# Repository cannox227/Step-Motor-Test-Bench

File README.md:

# Step-motor-test-bench

Step Motor Testbench is a tool made in collaboration with [ProM Facility](https://promfacility.eu/#/) which can be used to measure the __maximum power__ and the __maximum torque__ of a step motor. <br>
Notice that this is a prototype made up to validate the innovative company idea. 

## Functionalities
1. Driving the stepper motor
2. Driving the magnetic brake
3. Measuring the involved physical quantities such as: torque, voltage and current of the motor
4. Set the motor driver parameters and show the plots related to the obtained motor curves using a GUI (Graphical User Interface)

## Main components
- Step motor (device under test)
- Torque sensor
- Magnetic brake
- Master unit made of
    - Nucleo STM32 F7 Board
    - Custom PCB to handle different voltages and conditionate the signals
- Slave unit made of
    - Nucleo STM32 F4 Board
    - STM X-NUCLEO-IHM03A1 stepper driver extension board

## System block diagram

## Thesis abstract
This thesis reports the work done during my internship period at ProM Facility, the company - based in Rovereto (TN) - is focused on mechanics, electronics and informatics prototyping. This work principally covers the high level software development and at the same time the baremetal firmware development to support the innovative company project. In particular, ProM Facility had the necessity to prototype a __stepper motor test bench__ for an internal usage. This measurement tool is able to determine the __maximum power__ and __maximum torque__ provided by the under test motor.

At my arrival in the company the test bench mechanical structure was already built, ensuring the connection between a magnetic brake, a torque sensor and a stepper motor. To make the prototype actually working it has been necessary to integrate the hardware development with the software one. Obtaining the characteristic curves that describes the performance of the motor has been one of the main objectives of my work, in order to get this results sensors of voltage, current and torque have been used. Moreover, a wide variety of motor driver parameters selection has been implemented, in such a way to build a custom configuration with the purpose of optimize the produced curves by operating on the single parameters. However, this curve optimization task will be studied by the future company interns.

It has also been developed a dedicated graphical user interface to let the end user interacting with the test bench, with this software it is possible to change the motor driver parameters and test it under load; on the other hand, to read the sensors values and drive the motor, two units have been projected: _master_ and _slave_. The first one is made up of a _STM Nucleo F7_ board with a custom developed _shield_, where sensors and signal conditioning circuits have been soldered. The second one, instead, is composed of a _STM Nucleo F4_ board and an expansion driver board - the _STM X-NUCLEO-IHM03A1_ - necessary to control the motor under the F4 _microcontroller_ rules.

The thesis especially describes the development process to create the graphical interface using the Python programming language and to write the firmware of the master unit. For the last one a duo formed by the STM Cube MX software and the C language has been selected. Eventually, the remaining work, consisting of the slave firmware development and the prototyping of the expansion board for the master unit, has been up to the colleague with whom I have shared the internship experience, _Lisa Santarossa_.

As planned, the project has been concluded successfully, gathering the curves of __torque-power__ based on the custom configuration chosen by the end user.

__You can find the theseis [here](/Documentation/Tommaso_Canova_STB_thesis.pdf)__

## Repo structure
    ├── 📁 Documentation    -> media and thesis
    ├── 📁 Firmware         -> slave and master units firmware
    ├── 📁 GUI              -> graphical user iterface and plot scripts
    └── 📁 Hardware         -> custom master unit expansion board kicad project

## GUI screenshots
The GUI is made up of two main windows: the first one is used to control the motor driver parameters, to test the motor under load, to communicate with both units using serial communication and to save the acquired data into a csv file. The second one is used to plot the acquired data into some.

The second one is used to read the sensors values and to plot the acquired data in a dynamic way.

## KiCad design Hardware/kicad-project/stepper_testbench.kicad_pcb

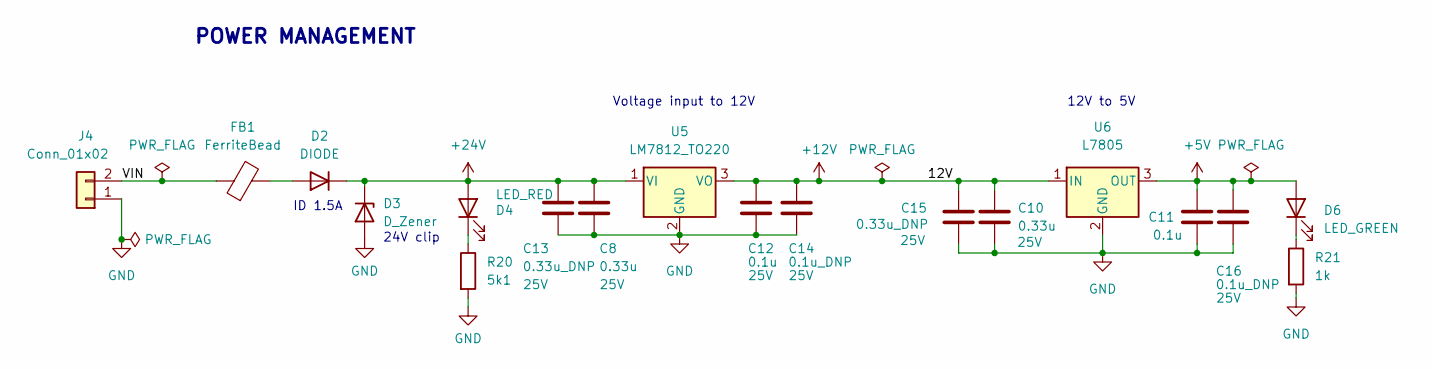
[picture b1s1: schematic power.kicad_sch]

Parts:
C8, C10: 0.33u; C_0603_1608Metric
C11, C12: 0.1u; C_0603_1608Metric
C13, C15: 0.33u_DNP; CP_Radial_D5.0mm_P2.50mm
C14, C16: 0.1u_DNP; CP_Radial_D5.0mm_P2.50mm
D2: DIODE; D_SOD-323
D3: D_Zener; D_SMA
D4: LED_RED; LED_0603_1608Metric
D6: LED_GREEN; LED_0603_1608Metric
FB1: FerriteBead; R_0805_2012Metric
J4: Conn_01x02; PinHeader_1x02_P2.54mm_Vertical
R20: 5k1; R_0603_1608Metric
R21: 1k; R_0603_1608Metric
U5: LM7812_TO220; TO-220-3_Vertical
U6: L7805; TO-220-3_Vertical

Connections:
+5V: C11.1, C16.1, D6.2 (A), U6.3 (OUT); also elsewhere on the board
+12V: C10.1, C12.1, C14.1, C15.1, U5.3 (VO), U6.1 (IN); also elsewhere on the board
+24V: C8.1, C13.1, D2.2 (K), D3.1 (K), D4.2 (A), U5.1 (VI); also elsewhere on the board
/Power/VIN: FB1.1, J4.2
GND: C8.2, C10.2, C11.2, C12.2, C13.2, C14.2, C15.2, C16.2, D3.2 (A), J4.1, R20.2, R21.2, U5.2 (GND), U6.2 (GND); also elsewhere on the board
unnamed: D2.1 (A), FB1.2
unnamed: D4.1 (K), R20.1
unnamed: D6.1 (K), R21.1

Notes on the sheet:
Voltage input to 12V
POWER MANAGEMENT
24V clip
12V to 5V
ID 1.5A

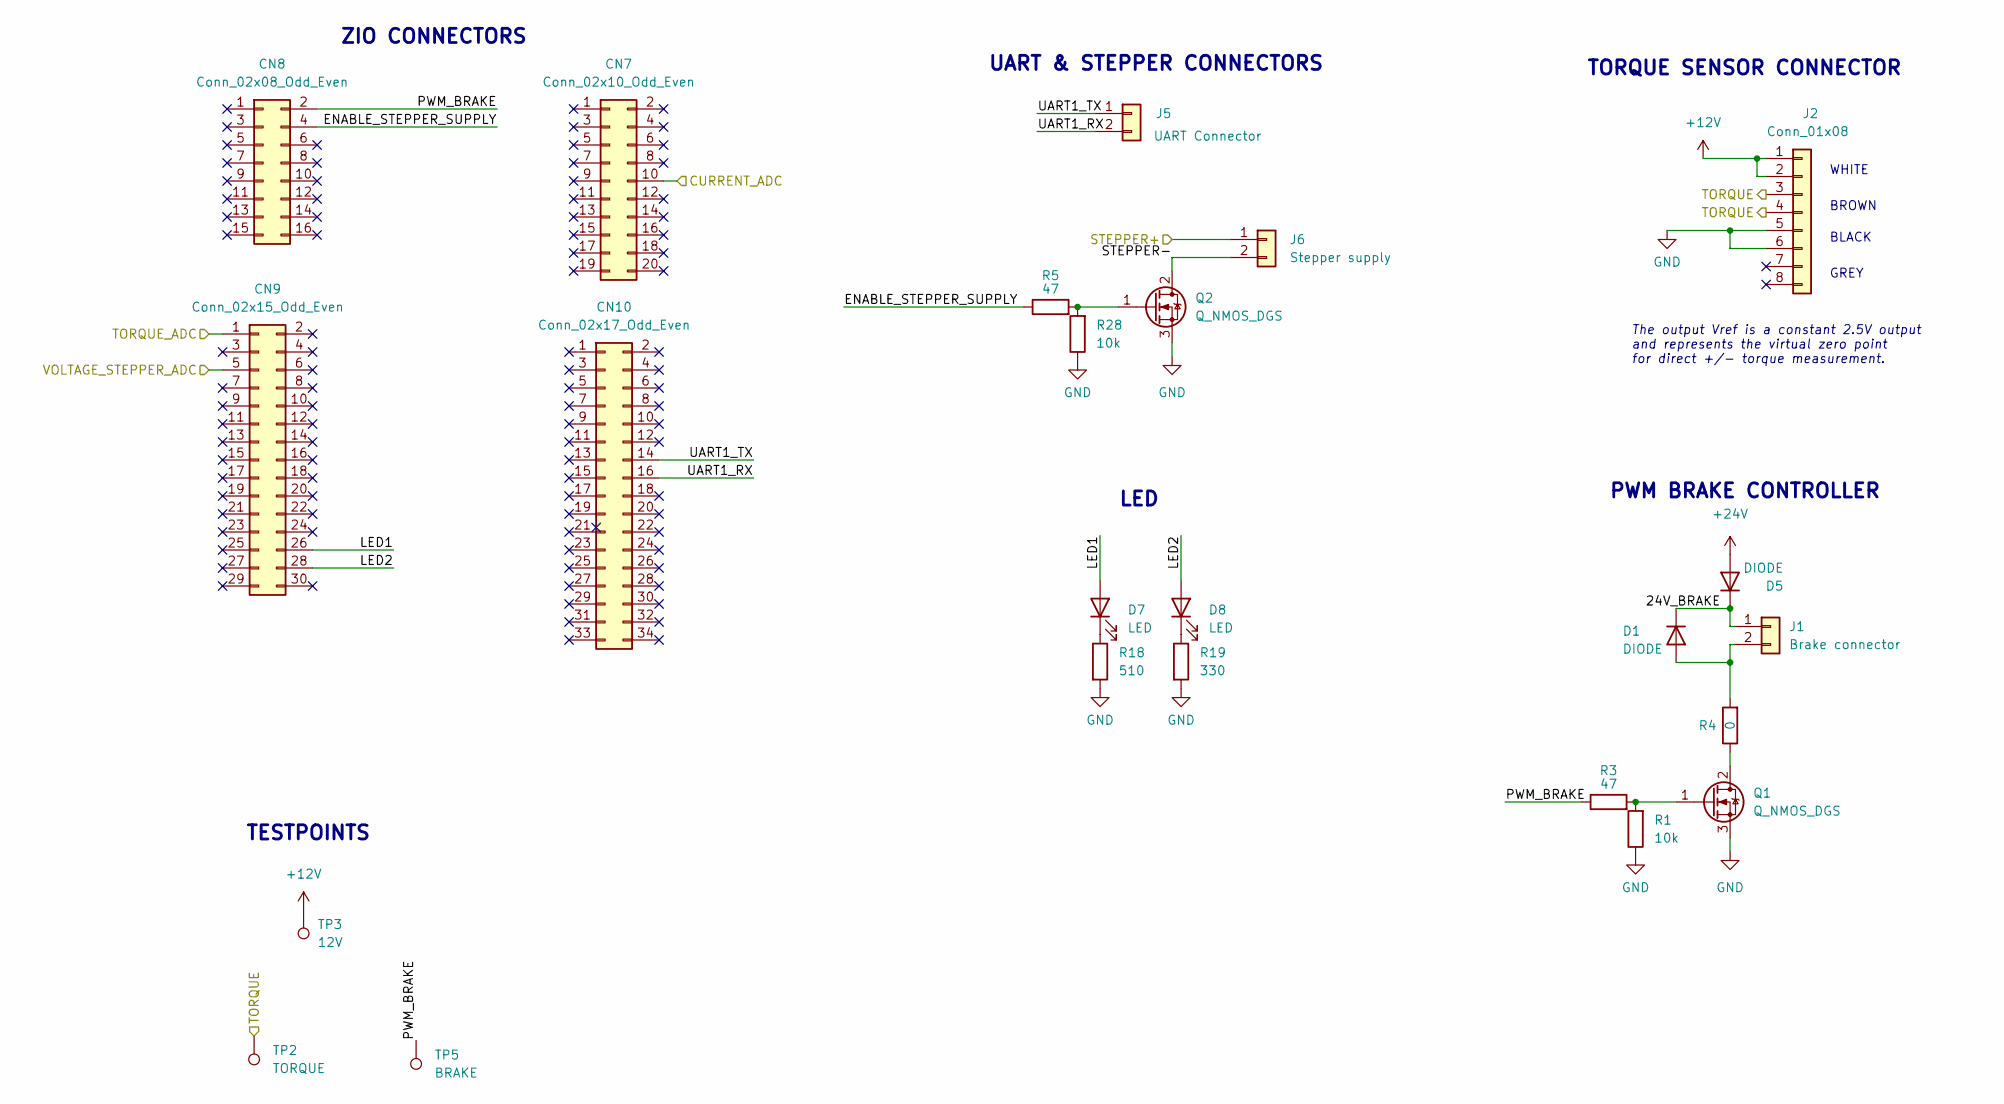
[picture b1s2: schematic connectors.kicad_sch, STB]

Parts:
CN7: Conn_02x10_Odd_Even; PinHeader_2x10_P2.54mm_Vertical
CN8: Conn_02x08_Odd_Even; PinHeader_2x08_P2.54mm_Vertical
CN9: Conn_02x15_Odd_Even; PinHeader_2x15_P2.54mm_Vertical
CN10: Conn_02x17_Odd_Even; PinHeader_2x17_P2.54mm_Vertical
D1, D5: DIODE; D_SOD-323
D7, D8: LED; LED_0603_1608Metric
J1: Brake connector; PinHeader_1x02_P2.54mm_Vertical
J2: Conn_01x08; PinHeader_1x08_P2.54mm_Vertical
J5: UART Connector; PinHeader_1x02_P2.54mm_Vertical
J6: Stepper supply; PinHeader_1x02_P2.54mm_Vertical
Q1, Q2: Q_NMOS_DGS; TO-252-2
R1, R28: 10k; R_0603_1608Metric
R3, R5: 47; R_0603_1608Metric
R4: 0; R_0603_1608Metric
R18: 510; R_0603_1608Metric
R19: 330; R_0603_1608Metric
TP2: TORQUE; TestPoint_Pad_D2.0mm
TP3: 12V; TestPoint_Pad_D2.0mm
TP5: BRAKE; TestPoint_Pad_D2.0mm

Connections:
+12V: J2.1, J2.2, TP3.1; also elsewhere on the board
+24V: D5.1 (A); also elsewhere on the board
/Connectors/24V_BRAKE: D1.2 (K), D5.2 (K), J1.1
/Connectors/ENABLE_STEPPER_SUPPLY: CN8.4, R5.1
/Connectors/LED1: CN9.26, D7.2 (A)
/Connectors/LED2: CN9.28, D8.2 (A)
/Connectors/PWM_BRAKE: CN8.2, R3.1, TP5.1
/Connectors/STEPPER+: J6.1; also elsewhere on the board
/Connectors/TORQUE: J2.3, J2.4, TP2.1; also elsewhere on the board
/Connectors/UART1_RX: CN10.16, J5.2
/Connectors/UART1_TX: CN10.14, J5.1
/Sensing/CURRENT_BUFF_ADC: CN7.10; also elsewhere on the board
/Sensing/TORQUE_BUFF_ADC: CN9.1; also elsewhere on the board
/Sensing/VOLTAGE_STEPPER_BUFF_ADC: CN9.5; also elsewhere on the board
GND: J2.5, J2.6, Q1.3 (S), Q2.3 (S), R1.1, R18.2, R19.2, R28.1; also elsewhere on the board
unnamed: D1.1 (A), J1.2, R4.2
unnamed: D7.1 (K), R18.1
unnamed: D8.1 (K), R19.1
unnamed: Q1.1 (G), R1.2, R3.2
unnamed: Q1.2 (D), R4.1
unnamed: Q2.1 (G), R5.2, R28.2
unnamed: J6.2, Q2.2 (D)

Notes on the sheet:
LED
TORQUE SENSOR CONNECTOR
BROWN
BLACK
WHITE
GREY
The output Vref is a constant 2.5V output and represents the virtual zero point for direct +/- torque measurement.
UART & STEPPER CONNECTORS
TESTPOINTS
ZIO CONNECTORS
PWM BRAKE CONTROLLER

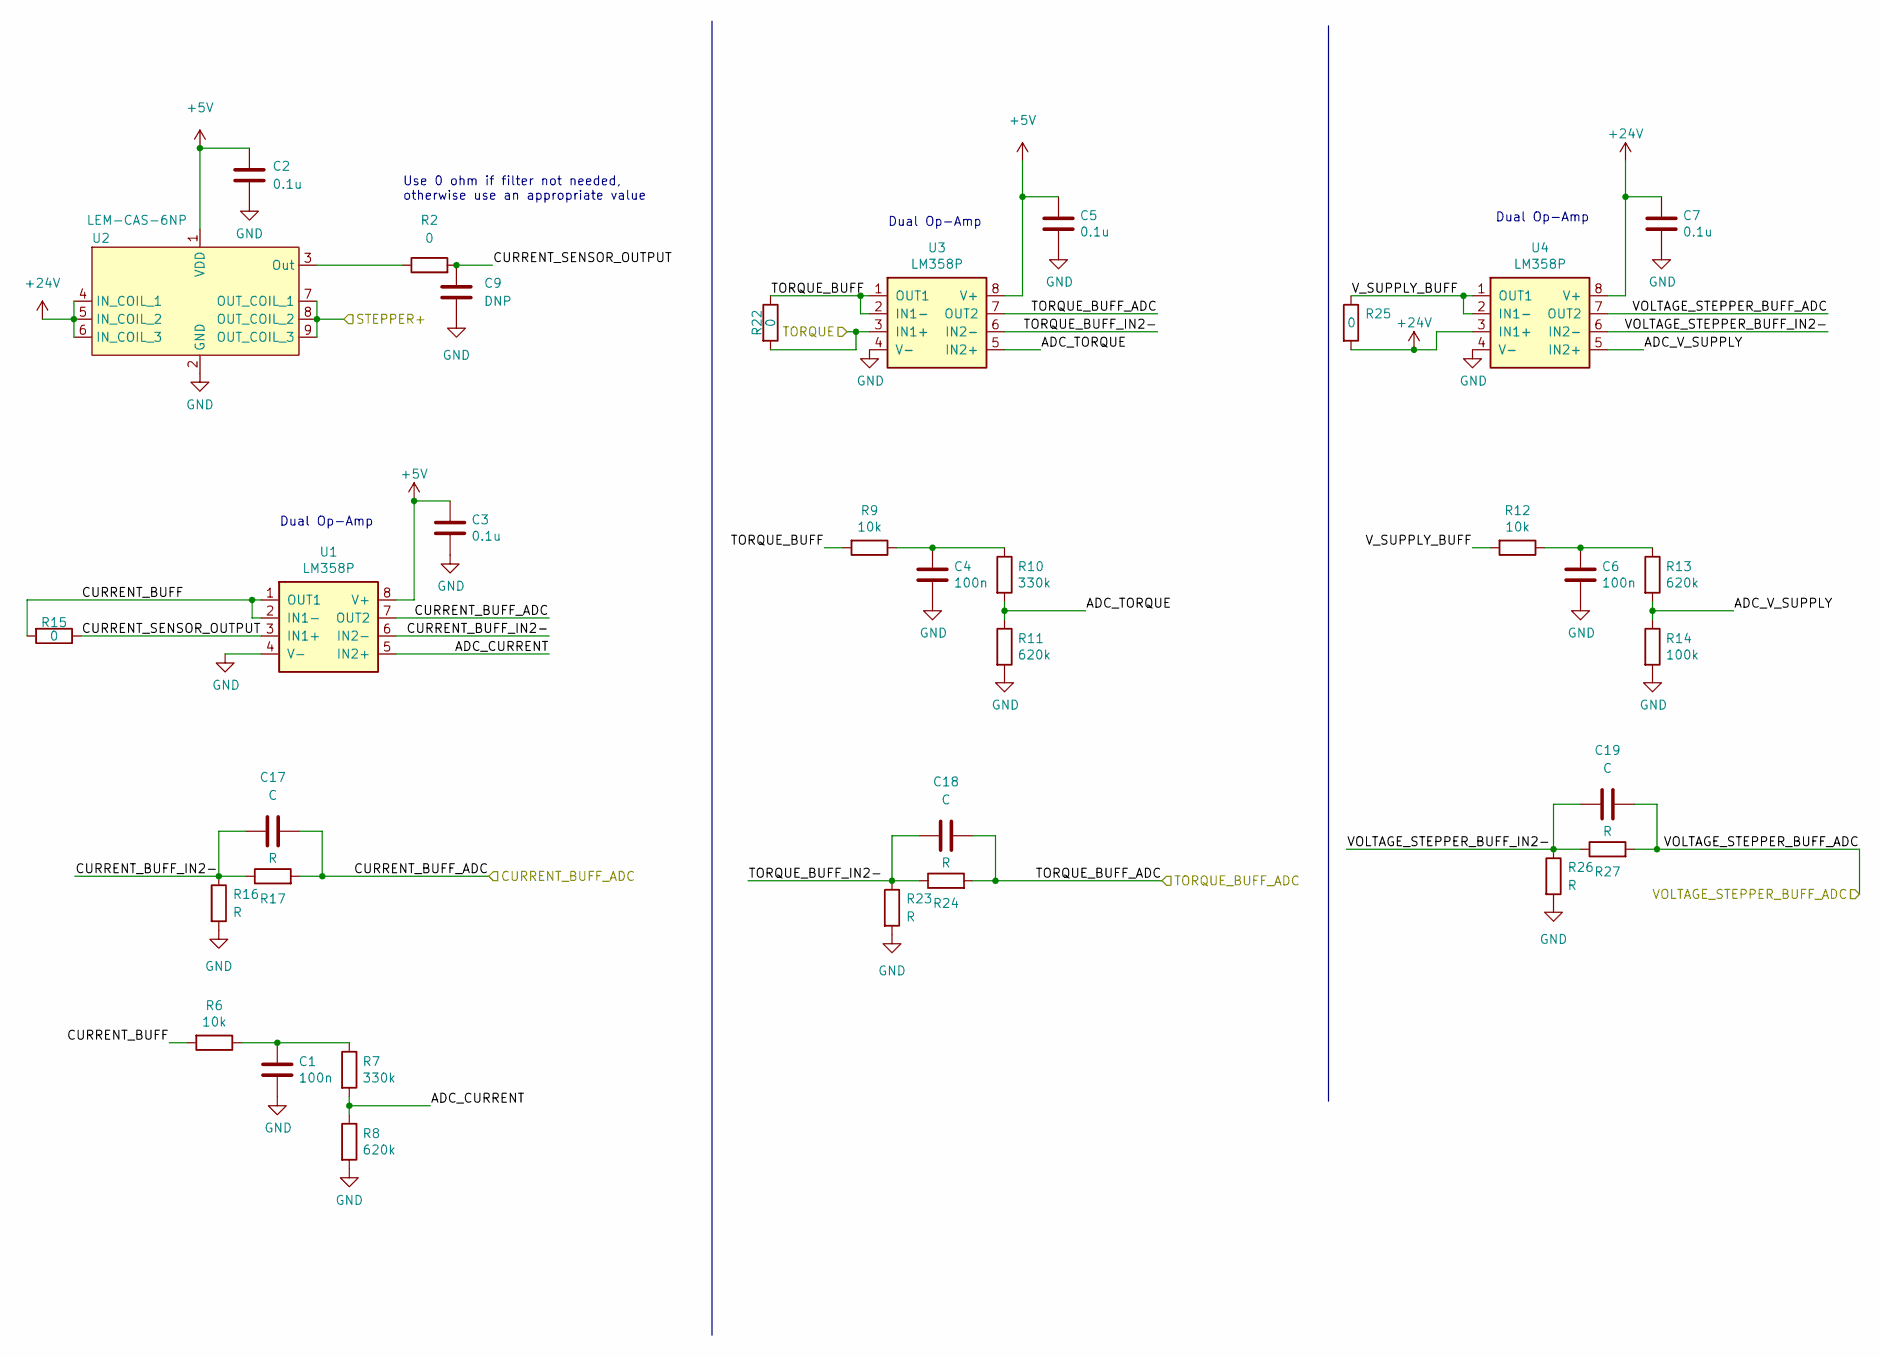
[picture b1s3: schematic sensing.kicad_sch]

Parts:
C1, C4, C6: 100n; C_0603_1608Metric
C2, C3, C5, C7: 0.1u; C_0603_1608Metric
C9: DNP; C_0805_2012Metric
C17, C18, C19: C; C_0805_2012Metric
R2, R15, R22, R25: 0; R_0603_1608Metric
R6, R9, R12: 10k; R_0603_1608Metric
R7, R10: 330k; R_0603_1608Metric
R8, R11, R13: 620k; R_0603_1608Metric
R14: 100k; R_0603_1608Metric
R16, R17, R23, R24, R26, R27: R; R_0603_1608Metric
U1, U3, U4: LM358P; DIP-8_W7.62mm
U2: LEM-CAS-6NP; LEM-CAS-6-NP

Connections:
+5V: C2.1, C3.1, C5.1, U1.8 (V+), U2.1 (VDD), U3.8 (V+); also elsewhere on the board
+24V: C7.1, R25.2, U2.4 (IN_COIL_1), U2.5 (IN_COIL_2), U2.6 (IN_COIL_3), U4.3 (IN1+), U4.8 (V+); also elsewhere on the board
/Connectors/STEPPER+: U2.7 (OUT_COIL_1), U2.8 (OUT_COIL_2), U2.9 (OUT_COIL_3); also elsewhere on the board
/Connectors/TORQUE: R22.2, U3.3 (IN1+); also elsewhere on the board
/Sensing/ADC_CURRENT: R7.2, R8.1, U1.5 (IN2+)
/Sensing/ADC_TORQUE: R10.2, R11.1, U3.5 (IN2+)
/Sensing/ADC_V_SUPPLY: R13.2, R14.1, U4.5 (IN2+)
/Sensing/CURRENT_BUFF: R6.2, R15.2, U1.1 (OUT1), U1.2 (IN1-)
/Sensing/CURRENT_BUFF_ADC: C17.1, R17.2, U1.7 (OUT2); also elsewhere on the board
/Sensing/CURRENT_BUFF_IN2-: C17.2, R16.1, R17.1, U1.6 (IN2-)
/Sensing/CURRENT_SENSOR_OUTPUT: C9.1, R2.2, R15.1, U1.3 (IN1+)
/Sensing/TORQUE_BUFF: R9.2, R22.1, U3.1 (OUT1), U3.2 (IN1-)
/Sensing/TORQUE_BUFF_ADC: C18.1, R24.2, U3.7 (OUT2); also elsewhere on the board
/Sensing/TORQUE_BUFF_IN2-: C18.2, R23.1, R24.1, U3.6 (IN2-)
/Sensing/VOLTAGE_STEPPER_BUFF_ADC: C19.1, R27.2, U4.7 (OUT2); also elsewhere on the board
/Sensing/VOLTAGE_STEPPER_BUFF_IN2-: C19.2, R26.1, R27.1, U4.6 (IN2-)
/Sensing/V_SUPPLY_BUFF: R12.2, R25.1, U4.1 (OUT1), U4.2 (IN1-)
GND: C1.2, C2.2, C3.2, C4.2, C5.2, C6.2, C7.2, C9.2, R8.2, R11.2, R14.2, R16.2, R23.2, R26.2, U1.4 (V-), U2.2 (GND), U3.4 (V-), U4.4 (V-); also elsewhere on the board
unnamed: C1.1, R6.1, R7.1
unnamed: C4.1, R9.1, R10.1
unnamed: C6.1, R12.1, R13.1
unnamed: R2.1, U2.3 (Out)

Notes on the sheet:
Dual Op-Amp
Use 0 ohm if filter not needed, otherwise use an appropriate value

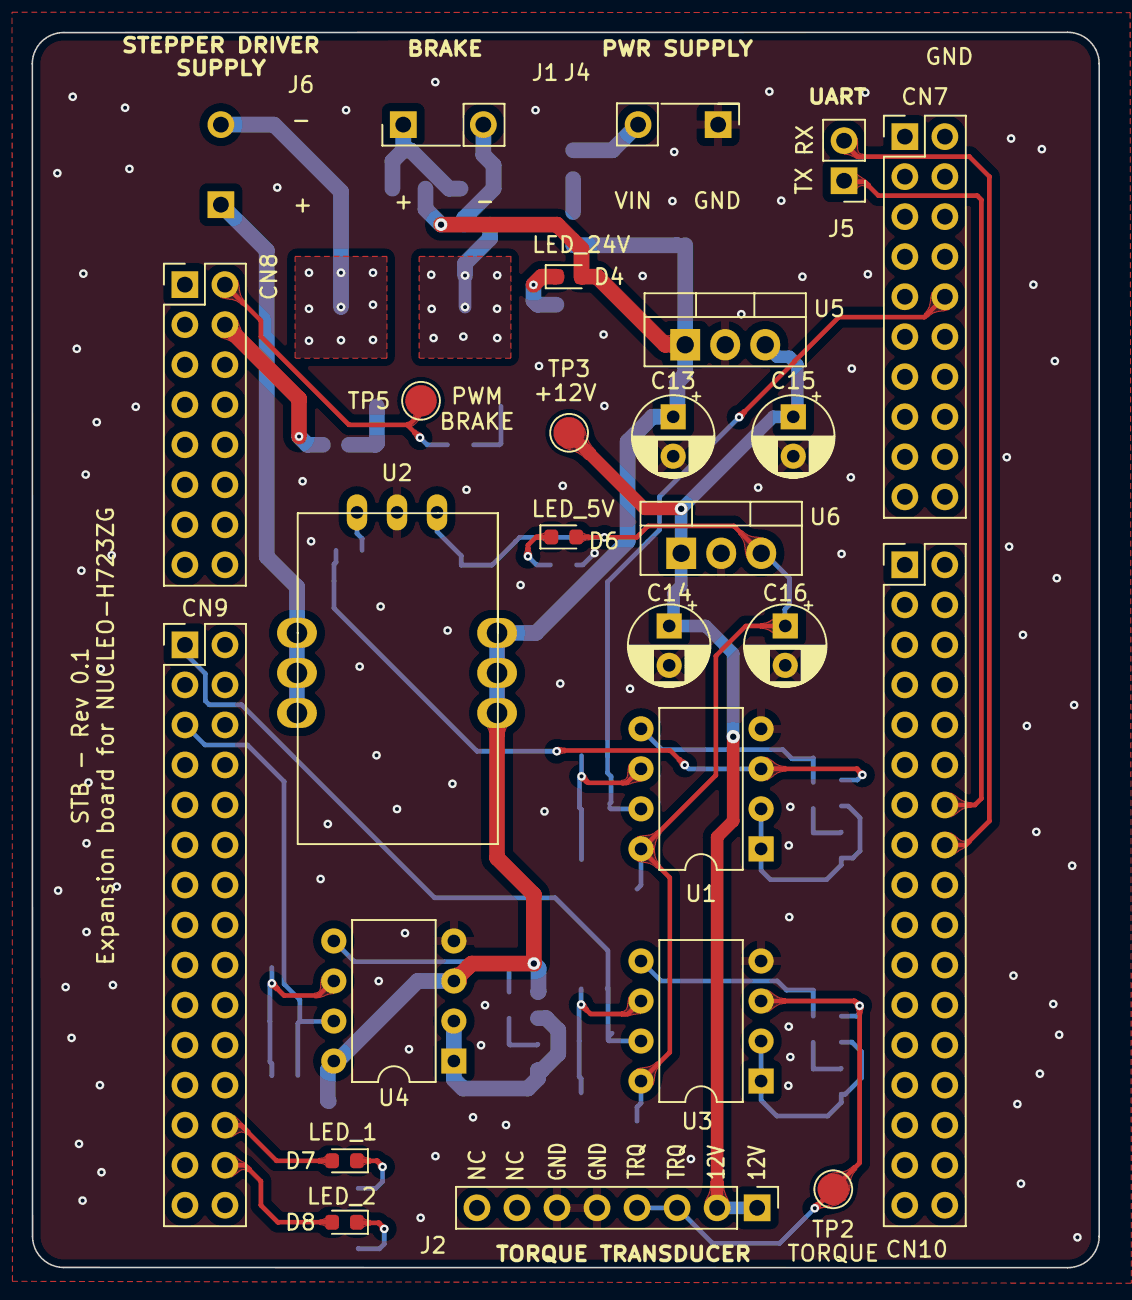
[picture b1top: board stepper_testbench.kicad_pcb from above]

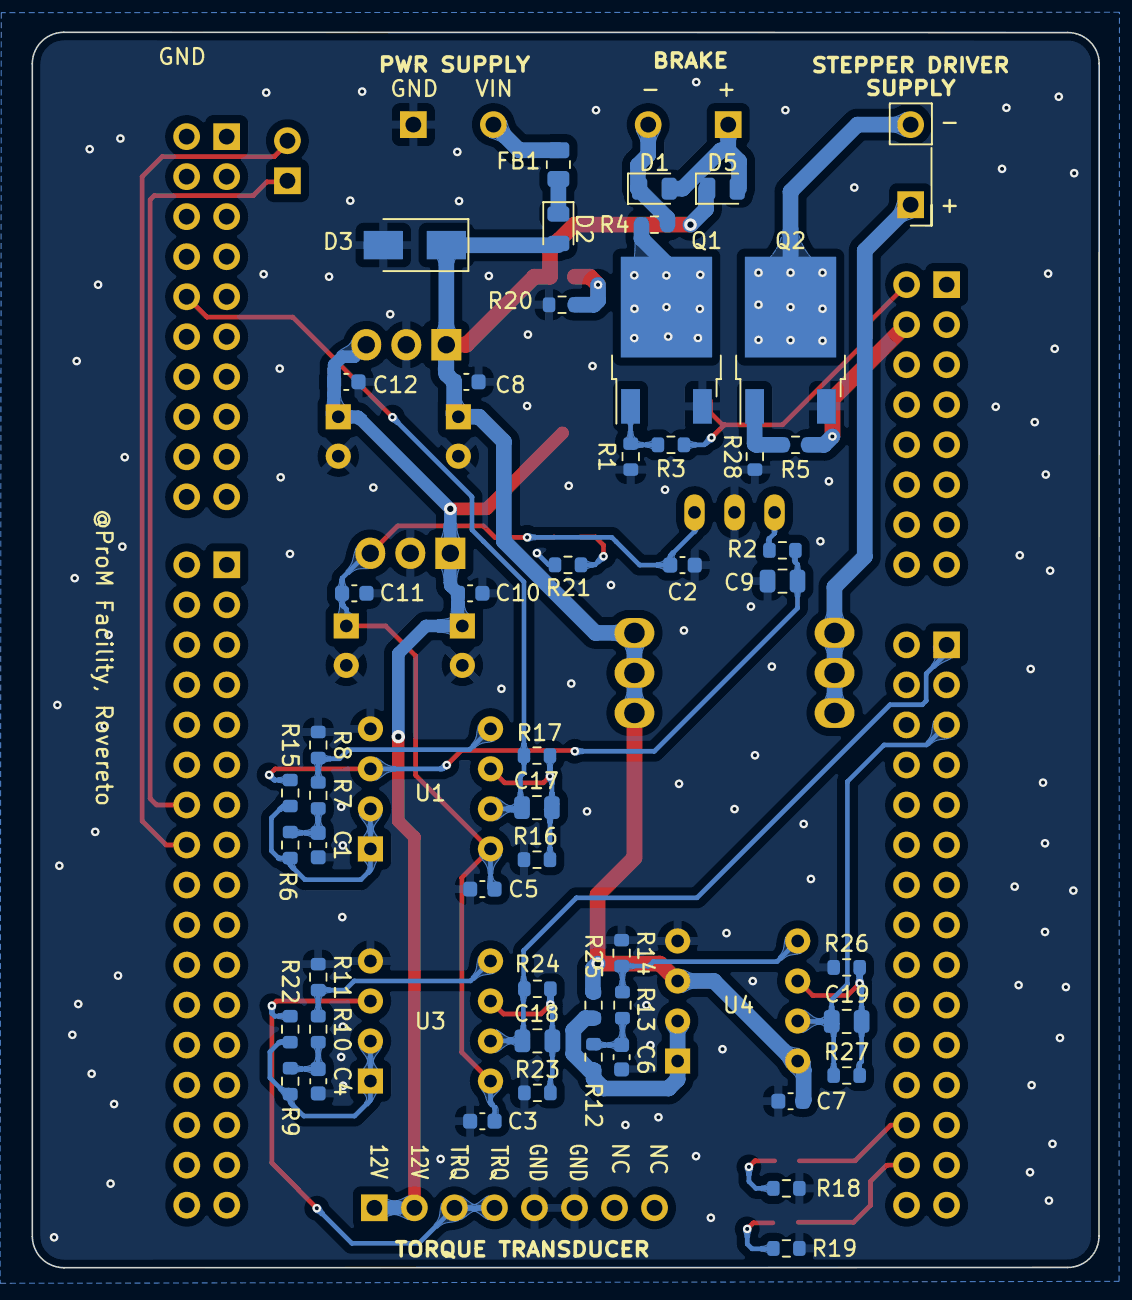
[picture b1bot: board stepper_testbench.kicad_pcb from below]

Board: 2 copper layers, 67.7 x 78.4 mm, 76 parts (55 on the bottom side), 41 nets.

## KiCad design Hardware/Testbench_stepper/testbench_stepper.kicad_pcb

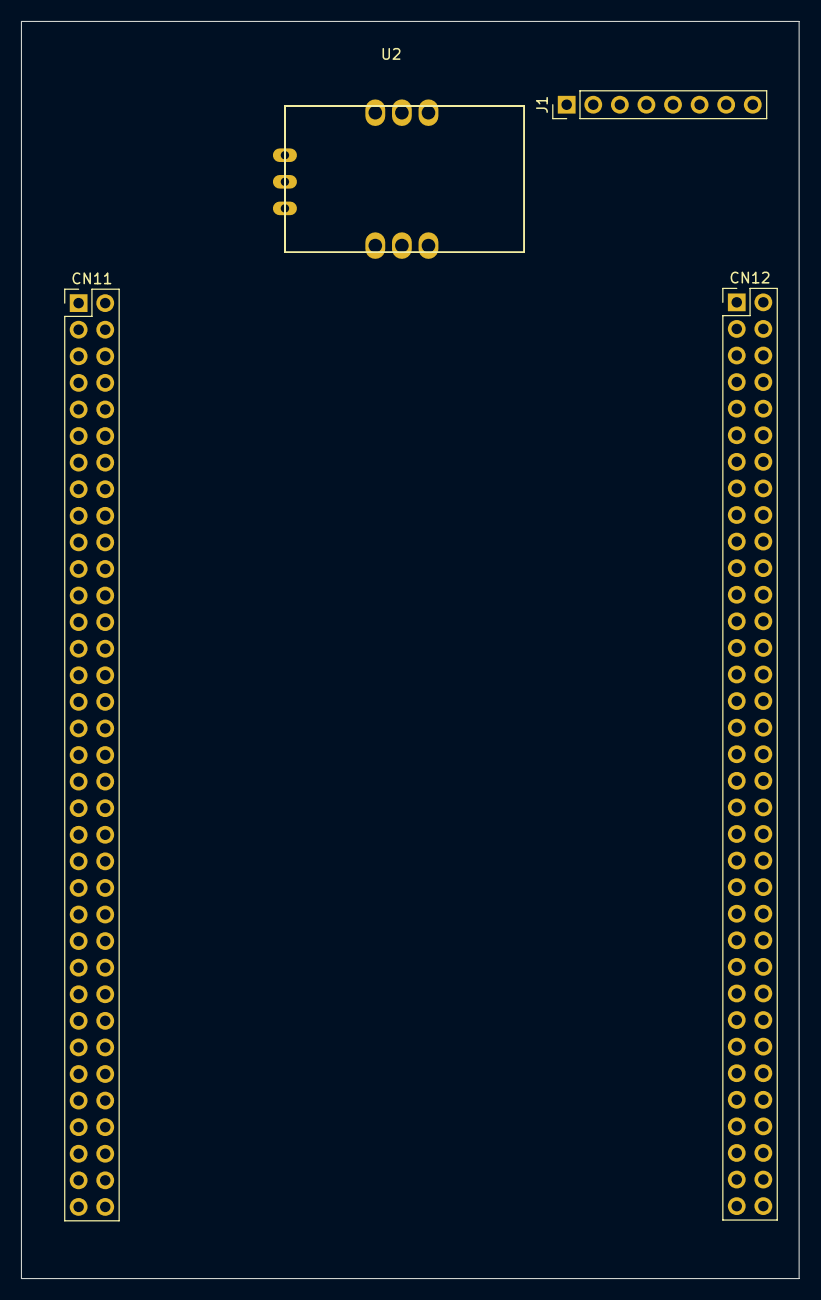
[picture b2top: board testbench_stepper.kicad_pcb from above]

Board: 2 copper layers, 74.3 x 120.1 mm, 4 parts (0 on the bottom side), 4 nets, no tracks yet.

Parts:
CN11, CN12: Conn_02x35_Odd_Even; PinHeader_2x35_P2.54mm_Vertical
J1: Conn_01x08_Male; PinHeader_1x08_P2.54mm_Vertical
U2: LEM-CAS-6-NP

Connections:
/Connectors/GND: J1.5, J1.6
/Connectors/TRQ: J1.3, J1.4
/Connectors/VDD: J1.1, J1.2
/Connectors/VREF: J1.7, J1.8

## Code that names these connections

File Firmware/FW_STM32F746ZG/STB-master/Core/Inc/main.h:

/* USER CODE BEGIN Header */
/**
  ******************************************************************************
  * @file           : main.h
  * @brief          : Header for main.c file.
  *                   This file contains the common defines of the application.
  ******************************************************************************
  * @attention
  *
  * Copyright (c) 2022 STMicroelectronics.
  * All rights reserved.
  *
  * This software is licensed under terms that can be found in the LICENSE file
  * in the root directory of this software component.
  * If no LICENSE file comes with this software, it is provided AS-IS.
  *
  ******************************************************************************
  */
/* USER CODE END Header */

/* Define to prevent recursive inclusion -------------------------------------*/
#ifndef __MAIN_H
#define __MAIN_H

#ifdef __cplusplus
extern "C" {
#endif

/* Includes ------------------------------------------------------------------*/
#include "stm32f7xx_hal.h"

/* Private includes ----------------------------------------------------------*/
/* USER CODE BEGIN Includes */
#include "tim.h"
/* USER CODE END Includes */

/* Exported types ------------------------------------------------------------*/
/* USER CODE BEGIN ET */

/* USER CODE END ET */

/* Exported constants --------------------------------------------------------*/
/* USER CODE BEGIN EC */

/* USER CODE END EC */

/* Exported macro ------------------------------------------------------------*/
/* USER CODE BEGIN EM */

/* USER CODE END EM */

/* Exported functions prototypes ---------------------------------------------*/
void Error_Handler(void);

/* USER CODE BEGIN EFP */
extern float brake_single_step_period;
/* USER CODE END EFP */

/* Private defines -----------------------------------------------------------*/
#define USER_Btn_Pin GPIO_PIN_13
#define USER_Btn_GPIO_Port GPIOC
#define LED1_Pin GPIO_PIN_7
#define LED1_GPIO_Port GPIOF
#define LED2_Pin GPIO_PIN_9
#define LED2_GPIO_Port GPIOF
#define MCO_Pin GPIO_PIN_0
#define MCO_GPIO_Port GPIOH
#define STEPPER_VOLTAGE_ADC_Pin GPIO_PIN_3
#define STEPPER_VOLTAGE_ADC_GPIO_Port GPIOC
#define TORQUE_ADC_Pin GPIO_PIN_3
#define TORQUE_ADC_GPIO_Port GPIOA
#define CURRENT_ADC_Pin GPIO_PIN_5
#define CURRENT_ADC_GPIO_Port GPIOA
#define LD1_Pin GPIO_PIN_0
#define LD1_GPIO_Port GPIOB
#define DEBUG_SIGNAL_2_Pin GPIO_PIN_0
#define DEBUG_SIGNAL_2_GPIO_Port GPIOG
#define LD3_Pin GPIO_PIN_14
#define LD3_GPIO_Port GPIOB
#define STLK_RX_Pin GPIO_PIN_8
#define STLK_RX_GPIO_Port GPIOD
#define STLK_TX_Pin GPIO_PIN_9
#define STLK_TX_GPIO_Port GPIOD
#define USB_PowerSwitchOn_Pin GPIO_PIN_6
#define USB_PowerSwitchOn_GPIO_Port GPIOG
#define USB_OverCurrent_Pin GPIO_PIN_7
#define USB_OverCurrent_GPIO_Port GPIOG
#define PWM_BRAKE_Pin GPIO_PIN_8
#define PWM_BRAKE_GPIO_Port GPIOC
#define ENABLE_STEPPER_SUPPLY_Pin GPIO_PIN_9
#define ENABLE_STEPPER_SUPPLY_GPIO_Port GPIOC
#define TMS_Pin GPIO_PIN_13
#define TMS_GPIO_Port GPIOA
#define TCK_Pin GPIO_PIN_14
#define TCK_GPIO_Port GPIOA
#define DEBUG_SIGNAL_1_Pin GPIO_PIN_0
#define DEBUG_SIGNAL_1_GPIO_Port GPIOD
#define SW0_Pin GPIO_PIN_3
#define SW0_GPIO_Port GPIOB
#define LD2_Pin GPIO_PIN_7
#define LD2_GPIO_Port GPIOB
/* USER CODE BEGIN Private defines */
#define UART_USB                          huart3
#define UART_SLAVE                        huart6
#define TIMER_BRAKE_PWM                   htim3
#define TIMER_BRAKE_PWM_CHANNEL           TIM_CHANNEL_3
#define TIMER_ADC_TRIGGER_CONVERSIONS     htim1
#define TIMER_ADC_CHANNEL_CURRENT_TRIGGER TIM_CHANNEL_1
#define TIMER_ADC_CHANNEL_TORQUE_TRIGGER  TIM_CHANNEL_2
#define TIMER_ADC_CHANNEL_VOLTAGE_TRIGGER TIM_CHANNEL_3
#define TIMER_BRAKE_STEP_CONTROL          htim6
#define ADC_CURRENT                       hadc2
#define ADC_TORQUE                        hadc1
#define ADC_VOLTAGE                       hadc3
#define DMA_CURRENT                       hdma_adc1
#define DMA_TORQUE                        hdma_adc2
#define DMA_VOLTAGE                       hdma_adc3

// #define TIMER_BRAKE_STEP_CONTROL                htim2
// #define TIMER_BRAKE_STEP_CONTROL_CHANNEL        TIM_CHANNEL_1
// #define TIMER_BRAKE_STEP_CONTROL_ACTIVE_CHANNEL HAL_TIM_ACTIVE_CHANNEL_1

#define MAX_STEPPER_SUPPLY 24
/* USER CODE END Private defines */

#ifdef __cplusplus
}
#endif

#endif /* __MAIN_H */

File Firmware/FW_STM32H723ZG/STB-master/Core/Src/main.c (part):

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uint32_t deadline              = 0;

// ADC variables
volatile float torque_gpio;
volatile float board_voltage;
volatile float stepper_current;
char adc_out[100];
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    
    */

    HAL_GPIO_WritePin(ENABLE_STEPPER_SUPPLY_GPIO_Port, ENABLE_STEPPER_SUPPLY_Pin, GPIO_PIN_RESET);
    memset(adc_out, 0x00, sizeof(adc_out));
    brake_init(&magnetic_brake);
    brake_set_pwm_duty_cycle(&magnetic_brake, 0.5);
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void HAL_GPIO_EXTI_Callback(uint16_t pin) {
    if (pin == BLUE_BUTTON_Pin) {
        (stepper.is_powered)
            ? HAL_GPIO_WritePin(ENABLE_STEPPER_SUPPLY_GPIO_Port, ENABLE_STEPPER_SUPPLY_Pin, GPIO_PIN_RESET)
            : HAL_GPIO_WritePin(ENABLE_STEPPER_SUPPLY_GPIO_Port, ENABLE_STEPPER_SUPPLY_Pin, GPIO_PIN_SET);
        stepper.is_powered = !stepper.is_powered;
    }
}

void update_sensor_values() {
    torque_gpio     = ADC_get_voltage_to_gpio_level();
    board_voltage   = ADC_get_voltage_converted();
    stepper_current = ADC_get_current_converted();
}

void update_sensor_values_and_print() {
    torque_gpio     = ADC_get_voltage_to_gpio_level();
    board_voltage   = ADC_get_voltage_converted();
    stepper_current = ADC_get_current_converted();

    sprintf(
        adc_out, "Current: %.2f A | STB supply: %.2f V | Trq: %.2f \r\n", stepper_current, board_voltage, torque_gpio);
    HAL_UART_Transmit(&UART_USB, (uint8_t *)adc_out, sizeof(adc_out), 100);
}

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
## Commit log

2021-12-09 features: basic dashboard with save option
2021-12-10 fix: typos
2021-12-10 plot: adding more window
2021-12-11 plot: dynamic plot implemented
2021-12-12 r/w: implemented r/w with different files
2021-12-13 fix: missing radio button read & errors handling
2022-03-18 Moved python code to GUI folder
2022-03-18 Deleted src folder
2022-03-18 rm ds_store
2022-03-18 Added cube IDE project
2022-03-21 readme update
2022-03-22 Moved fw board into FW_STM32F4 folder
2022-03-22 Moved .project files into FW_STM32F4 folder
2022-03-22 Moved readme
2022-03-22 other: removed useless folders
2022-07-22 add kicad project
2022-07-23 hw: schematic update
2022-07-25 fw: add led state pin to ioc
2022-07-25 hw: dix schematic conflict
2022-07-25 hw: fix pcb conflict
2022-07-26 hw: first pcb routing
2022-07-26 hw: update layout corrections
2022-07-26 fw: add pwm output
2022-07-26 hw: add bom
2022-07-27 hw: add round corners and credits
2022-07-27 hw: add library folder
2022-07-27 hw: update layout with right screw terminal
2022-07-27 hw: update layout
2022-07-27 change 24V zener footprint to SMA
2022-07-27 hw: sch update
2022-07-27 fw+gui: add basic serial communication between GUI and MCU
2022-07-28 gui: add custom cmd sending
2022-07-28 fw: add stb master readme with flowchart
2022-07-28 hw: final pdf schematic upload
2022-07-28 fw: h7 ioc update
2022-07-28 GUI: add motor models file
2022-07-28 hw: layout v0.1.1
2022-07-28 hw: layout v0.1.2
2022-07-28 hw: add gerber files
2022-07-28 fw: ioc update
2022-07-28 GUI: add some params for voltage and current mode
2022-07-30 GUI: improved file management + motor configuration
2022-07-30 GUI: fix read error
2022-07-31 GUI: show device name when serial socket is open
2022-08-01 chore: gitignore update
2022-08-01 fw: add nucleo f401re playground for GUI testing
2022-08-01 GUI: add double serial interface panel for master and slave communication
2022-08-01 GUI: add <print_current_config> button
2022-08-01 GUI+fw: add basic float rx for slave device
2022-08-02 slave branch initial commit
2022-08-02 GUI: add brake buttons
2022-08-02 fw: add magnetic brake utils
2022-08-03 fw: task powerstep added but not working
2022-08-03 fw: remove F4 folder
2022-08-03 fw: add clean F4 folder
2022-08-03 fw: clean F4 folder pt2
2022-08-04 fw: checkpoint, basic config with stepper and serial working fine
2022-08-04 fw: add Drivers folder
2022-08-04 GUI: add fw/bw/hd/st/gt/gh buttons with cmd generation
2022-08-05 GUI: change motor generic commands to horizontal layout
2022-08-05 GUI: add dynamic text with pwm value received by master
2022-08-05 fw: add state machine + tx pwm value to gui
2022-08-05 fw: add other serial task (to_master)
2022-08-05 GUI: add automatic test button
2022-08-05 fw: add automatic test between master and slave
2022-08-07 GUI: add all common parameters with enum implementation
2022-08-07 GUI: change working mode (voltage/current) following powerstep01_CmVm_t enum
2022-08-07 GUI: add decay/fall enums in current params
2022-08-07 GUI: add motor config serialization (to be tested)
2022-08-09 fw master: add basic adc conversion + fix dma issue changing .ld file
2022-08-10 fw slave: fix concurrent threads error with timeslice assignment
2022-08-17 fw f7/f4: add tiny stb project with torque adc read
2022-08-17 gitignore: ignore csv files
2022-08-17 GUI: BREAKING CHANGE - add thread and basic w/r csv based on torque value
2022-08-18 gitignore update
2022-08-18 plot: add script to read and store plot as pdf
2022-08-18 GUI: add another interface to plot from a csv
2022-08-18 GUI: split acquisition from plot into two separate gui
2022-08-18 plot_script: add keyword to read last csv added
2022-08-19 plot_script: change specific column reference with an iteration approach
2022-08-22 GUI: readme + dependencies update
2022-08-23 FW master: BREAKING CHANGE -> moved to STM32F746ZG (adc meas tested)
2022-08-23 GUI+FW: automated test basic version (no timer)
2022-08-25 fw+GUI: working prototype with automatic test
2022-08-25 fw+GUI: add manual test with adc output functionality
2022-08-25 fw: reduce ack time + add debug signals
2022-08-26 fix: adc trigger timer is now at 200 Hz
2022-08-30 fw: add enable stepper supply before
2022-08-30 fix: add drivers folder
2022-08-30 GUI: general updates
2022-10-20 BREAKING CHANGE: removed H7 board support
2022-10-20 chore: add Licence
2022-10-20 chore: add documentation
2022-10-20 BREAKING CHANGE: move to revised pcb layout
2022-10-20 chore: readme update

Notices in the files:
Firmware/FW_STM32H723ZG/STB-master/Core/Src/main.c:
© Copyright (c) 2022 STMicroelectronics.
All rights reserved.
This software component is licensed by ST under BSD 3-Clause license,
the "License"; You may not use this file except in compliance with the
License. You may obtain a copy of the License at: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
(C) COPYRIGHT STMicroelectronics *****END OF FILE
